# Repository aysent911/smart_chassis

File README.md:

# Smart Chassis
Smart Chassis platform for robotics and remote applications.  
## Control Server
ESP01-based webserver accessible via Wi-Fi for controlling chassis manouvres:  
forwarding, 
reversing,
soft braking, 
handBrake,
turning.

## Electronic Control Unit
Atmega328p powered unit with H bridge DC motor driver, servo motor, power converters and connectors

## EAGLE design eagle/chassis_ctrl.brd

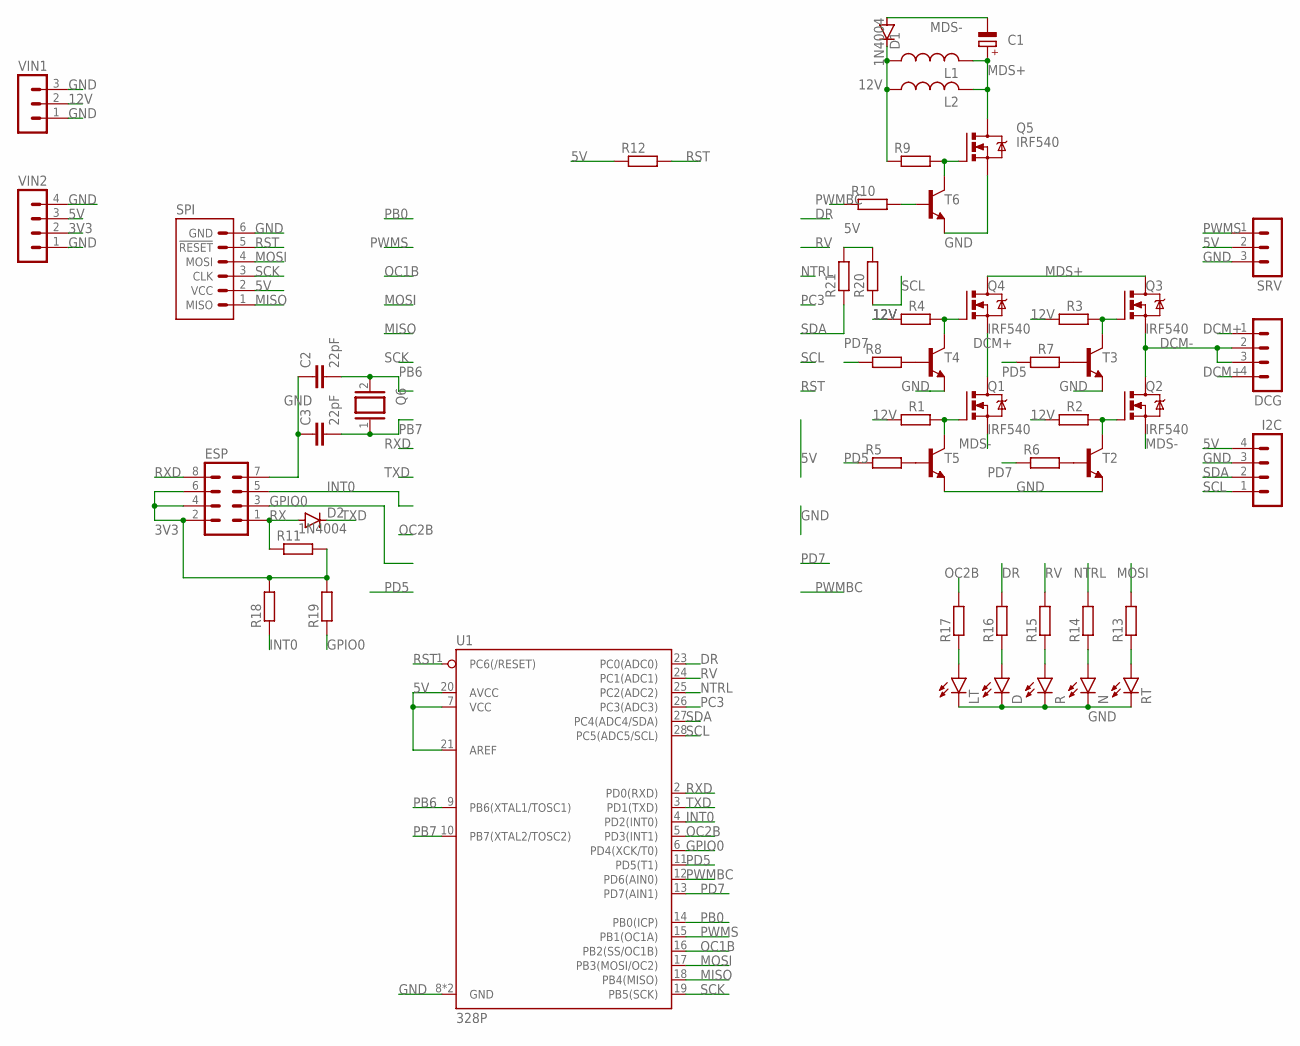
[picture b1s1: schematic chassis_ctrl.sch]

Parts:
C1: CPOL-EUE5-10.5; E5-10,5
C2, C3: 22pF; CAP-PTH-2.54
D: LED5MM
D1, D2: 1N4004; DO41-10
DCG: MA04-1
ESP: MA04-2
I2C: MA04-1
L1, L2: L-US0204V; 0204V
LT: LED5MM
N: LED5MM
Q1, Q2, Q3, Q4, Q5: IRF540; TO220BV
Q6: XTAL/S; QS
R: LED5MM
R1, R2, R3, R4, R5, R6, R7, R8, R9, R10, R11, R12, R13, R14, R15, R16, R17, R18, R19, R20, R21: R-EU_0207/10; 0207/10
RT: LED5MM
SPI: MISO_MOSITHT_100MIL; PINHEADER_2R03_100MIL
SRV: MA03-1
T2, T3, T4, T5, T6: 2N2222-NPN-TO92-EBC; TO92-EBC
U1: 328P; DIP28
VIN1: MA03-1
VIN2: MA04-1

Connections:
3V3: ESP.2, ESP.4, ESP.6, R11.2, R18.2, R19.2, VIN2.2
5V: I2C.4, R12.1, R20.2, R21.2, SPI.2 (VCC), SRV.2, U1.7 (VCC), U1.20 (AVCC), U1.21 (AREF), VIN2.3
12V: D1.C, L1.1, L2.1, R1.1, R2.1, R3.1, R4.1, R9.1, VIN1.2
DCM+: DCG.1, DCG.4, Q1.D, Q4.S
DCM-: DCG.2, DCG.3, Q2.D, Q3.S
DR: R16.2, U1.23 (PC0(ADC0))
GND: C2.1, C3.1, D.K (C), ESP.7, I2C.3, LT.K (C), N.K (C), Q5.S, R.K (C), RT.K (C), SPI.6 (GND), SRV.3, T2.E, T3.E, T4.E, T5.E, T6.E, U1.8 (GND), U1.22 (GND), VIN1.1, VIN1.3, VIN2.1, VIN2.4
GPIO0: ESP.3, R19.1, U1.6 (PD4(XCK/T0))
INT0: ESP.5, R18.1, U1.4 (PD2(INT0))
MDS+: C1.+, L1.2, L2.2, Q3.D, Q4.D, Q5.D
MDS-: C1.-, D1.A, Q1.S, Q2.S
MISO: SPI.1 (MISO), U1.18 (PB4(MISO))
MOSI: R13.2, SPI.4 (MOSI), U1.17 (PB3(MOSI/OC2))
unnamed: LT.A, R17.1
unnamed: D.A, R16.1
unnamed: R.A, R15.1
unnamed: N.A, R14.1
unnamed: R13.1, RT.A
unnamed: Q2.G, R2.2, T2.C
unnamed: Q1.G, R1.2, T5.C
unnamed: Q3.G, R3.2, T3.C
unnamed: Q4.G, R4.2, T4.C
unnamed: R5.2, T5.B
unnamed: R7.2, T3.B
unnamed: R6.2, T2.B
unnamed: R8.2, T4.B
unnamed: Q5.G, R9.2, T6.C
unnamed: R10.2, T6.B
NTRL: R14.2, U1.25 (PC2(ADC2))
OC1B: U1.16 (PB2(SS/OC1B))
OC2B: R17.2, U1.5 (PD3(INT1))
PB0: U1.14 (PB0(ICP))
PB6: C2.2, Q6.2, U1.9 (PB6(XTAL1/TOSC1))
PB7: C3.2, Q6.1, U1.10 (PB7(XTAL2/TOSC2))
PC3: U1.26 (PC3(ADC3))
PD5: R5.1, R7.1, U1.11 (PD5(T1))
PD7: R6.1, R8.1, U1.13 (PD7(AIN1))
PWMBC: R10.1, U1.12 (PD6(AIN0))
PWMS: SRV.1, U1.15 (PB1(OC1A))
RST: R12.2, SPI.5 (!RESET), U1.1 (PC6(/RESET))
RV: R15.2, U1.24 (PC1(ADC1))
RX: D2.A, ESP.1, R11.1
RXD: ESP.8, U1.2 (PD0(RXD))
SCK: SPI.3 (CLK), U1.19 (PB5(SCK))
SCL: I2C.1, R20.1, U1.28 (PC5(ADC5/SCL))
SDA: I2C.2, R21.1, U1.27 (PC4(ADC4/SDA))
TXD: D2.C, U1.3 (PD1(TXD))

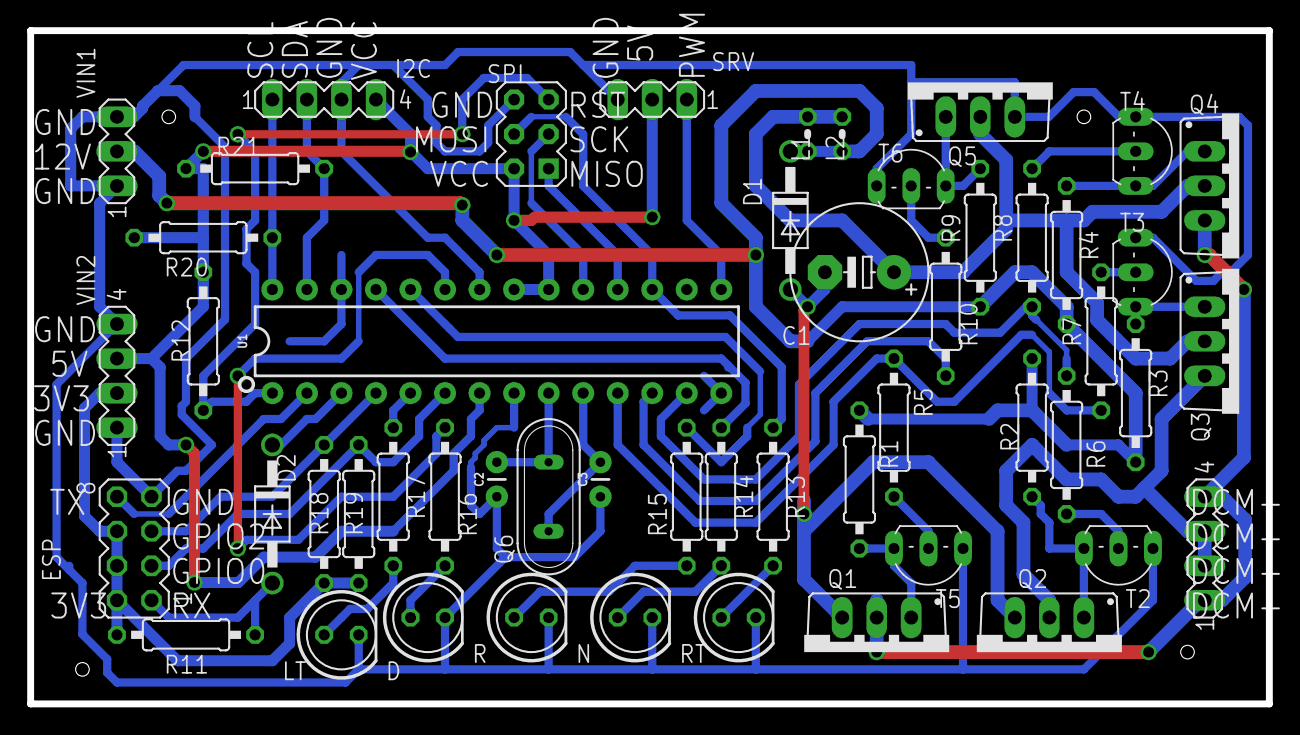
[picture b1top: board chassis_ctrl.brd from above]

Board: 2 copper layers, 91.1 x 49.5 mm, 52 parts (0 on the bottom side), 44 nets.

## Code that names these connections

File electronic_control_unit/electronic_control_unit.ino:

#include <Arduino.h>
#include <stdbool.h>
#include <string.h>
char ESP_response[50];
char mode[] = "setup";
char command = 9;
bool is_request = false;
void setup() {
  // put your setup code here, to run once:
  DDRD |= (0x20)|(0x80);  //set PD5(P-Channel1) and PD7(N-channel2) as output
  DDRB |= (0x01)|(0x04);  //set PB0(N-Channel1) and PB2(P-Channel2) as output
  //Hand brake/parking
  PORTD &= 0xDF;          //turn off P-Channel1
  PORTB &= 0xFB;          //turn off P-Channel2
  PORTD &= 0x7F;          //turn on N-Channel2
  PORTB &= 0xFE;          //turn on N-Channel1
  uart_init();
  
  sei();  
  DDRC |= (0x04)|(0x01);           //set PC0(Power) and PC2(Brake Light) as output
  DDRD |= 0x08;                  //set PD3 as Reverse Light output
  DDRB |= 0x08;                   //set PB3 as Reverse Light output       
  PORTC |= 0x01;                  //power output
  
  delay(5000);  //wait for devices to power up
  strcpy(mode, "main");
  //turn on Brake Light
  PORTC |= 0x04;
  //turn off reverese lights
  PORTD &= 0xF7;
  PORTB &= 0xF7;
}

void loop() {
  if(is_request){
    switch(command){
      case 'A':  //NEUTRAL
        PORTD &= 0xDF;          //turn off P-Channel1
        PORTB &= 0xFB;          //turn off P-Channel2
        PORTD |= 0x80;          //turn off N-Channel2
        PORTB |= 0x01;          //turn off N-Channel1
        //turn off Brake Light
        PORTC &= 0xFB;
        //turn off reverese lights
        PORTD &= 0xF7;
        PORTB &= 0xF7;
        is_request = false;
        break;
      
      case '1':  //REVERSE
        //neutral
        PORTD &= 0xDF;          //turn off P-Channel1
        PORTB &= 0xFB;          //turn off P-Channel2
        PORTD |= 0x80;          //turn off N-Channel2
        PORTB |= 0x01;          //turn off N-Channel1
        delay(25);
        //turn off Brake Light
        PORTC &= 0xFB;
        //turn on reverese lights
        PORTD |= 0x08;
        PORTB |= 0x08;
        //reverse
        PORTD |= 0x20;          //turn on P-Channel1
        PORTB &= 0xFE;          //turn on N-Channel1
        is_request = false;
        break;
  
      case '7': //Drive 1
        //neutral
        PORTD &= 0xDF;          //turn off P-Channel1
        PORTB &= 0xFB;          //turn off P-Channel2
        PORTD |= 0x80;          //turn off N-Channel2
        PORTB |= 0x01;          //turn off N-Channel1
        delay(25);
        //turn off Brake Light
        PORTC &= 0xFB;
        //turn off reverese lights
        PORTD &= 0xF7;
        PORTB &= 0xF7;
        //Drive 1
        PORTB |= 0x04;          //turn on P-Channel2
        PORTD &= 0x7F;          //turn on N-Channel2
        is_request = false;
        break;
        
      case '9': //Hand break/parking
        //neutral
        PORTD &= 0xDF;          //turn off P-Channel1
        PORTB &= 0xFB;          //turn off P-Channel2
        PORTD |= 0x80;          //turn off N-Channel2
        PORTB |= 0x01;          //turn off N-Channel1
        delay(25);
        //turn on Brake Light
        PORTC |= 0x04;
        //turn off reverese lights
        PORTD &= 0xF7;
        PORTB &= 0xF7;
        //hand brake/parking
        PORTD &= 0x7F;          //turn on N-Channel2
        PORTB &= 0xFE;          //turn on N-Channel1
        is_request = false;
        break;
        
      default:
        delay(25);
    }
  }
  delay(50);
}
//uart receive complete ISR
ISR(USART_RX_vect){
  char received_byte = UDR0;
  if (strcmp(mode,"setup") == 0){
    if (received_byte == '\n'){
      //clear ESP_response
      for(uint8_t i = 0; i < sizeof(ESP_response);i++){
        ESP_response[i] = '\0';
      }
    }else if((received_byte>=32)&&(received_byte<128)){
      strncat(ESP_response,&received_byte, 1);  
    }
  }
  else if (strcmp(mode,"main") == 0){
    //process request
    if(((received_byte >= '1')&&(received_byte <= '9'))||(received_byte == 'A')){
      command = received_byte;
      is_request = true;
    }
  }
}
void uart_init(){
  //clear RXC, TXC
  UCSR0A &= 0x3F;
  
  //enable RXC, RX and TX
  UCSR0B=(1<<RXCIE0)|(1<<RXEN0)|(1<<TXEN0);  
 
  //8bits,1 stop bit,asynchronous mode //,even parity
  UCSR0C=(1<<UCSZ01)|(1<<UCSZ00); 
  
  //9600 baud at 16MHz, UBRR = 103
  UBRR0L=103;
}

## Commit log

2025-08-01 added eagle PCB schematic

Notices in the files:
parts and their libraries:
SparkFun-Capacitors: Licensing: Creative Commons ShareAlike 4.0 International - https://creativecommons.org/licenses/by-sa/4.0
